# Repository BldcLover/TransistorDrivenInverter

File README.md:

# TransistorDrivenInverter
 Controlling mosfet using transistor logic.

 Here is the testing Video:
 https://youtube.com/shorts/wIxtIQQuSTw

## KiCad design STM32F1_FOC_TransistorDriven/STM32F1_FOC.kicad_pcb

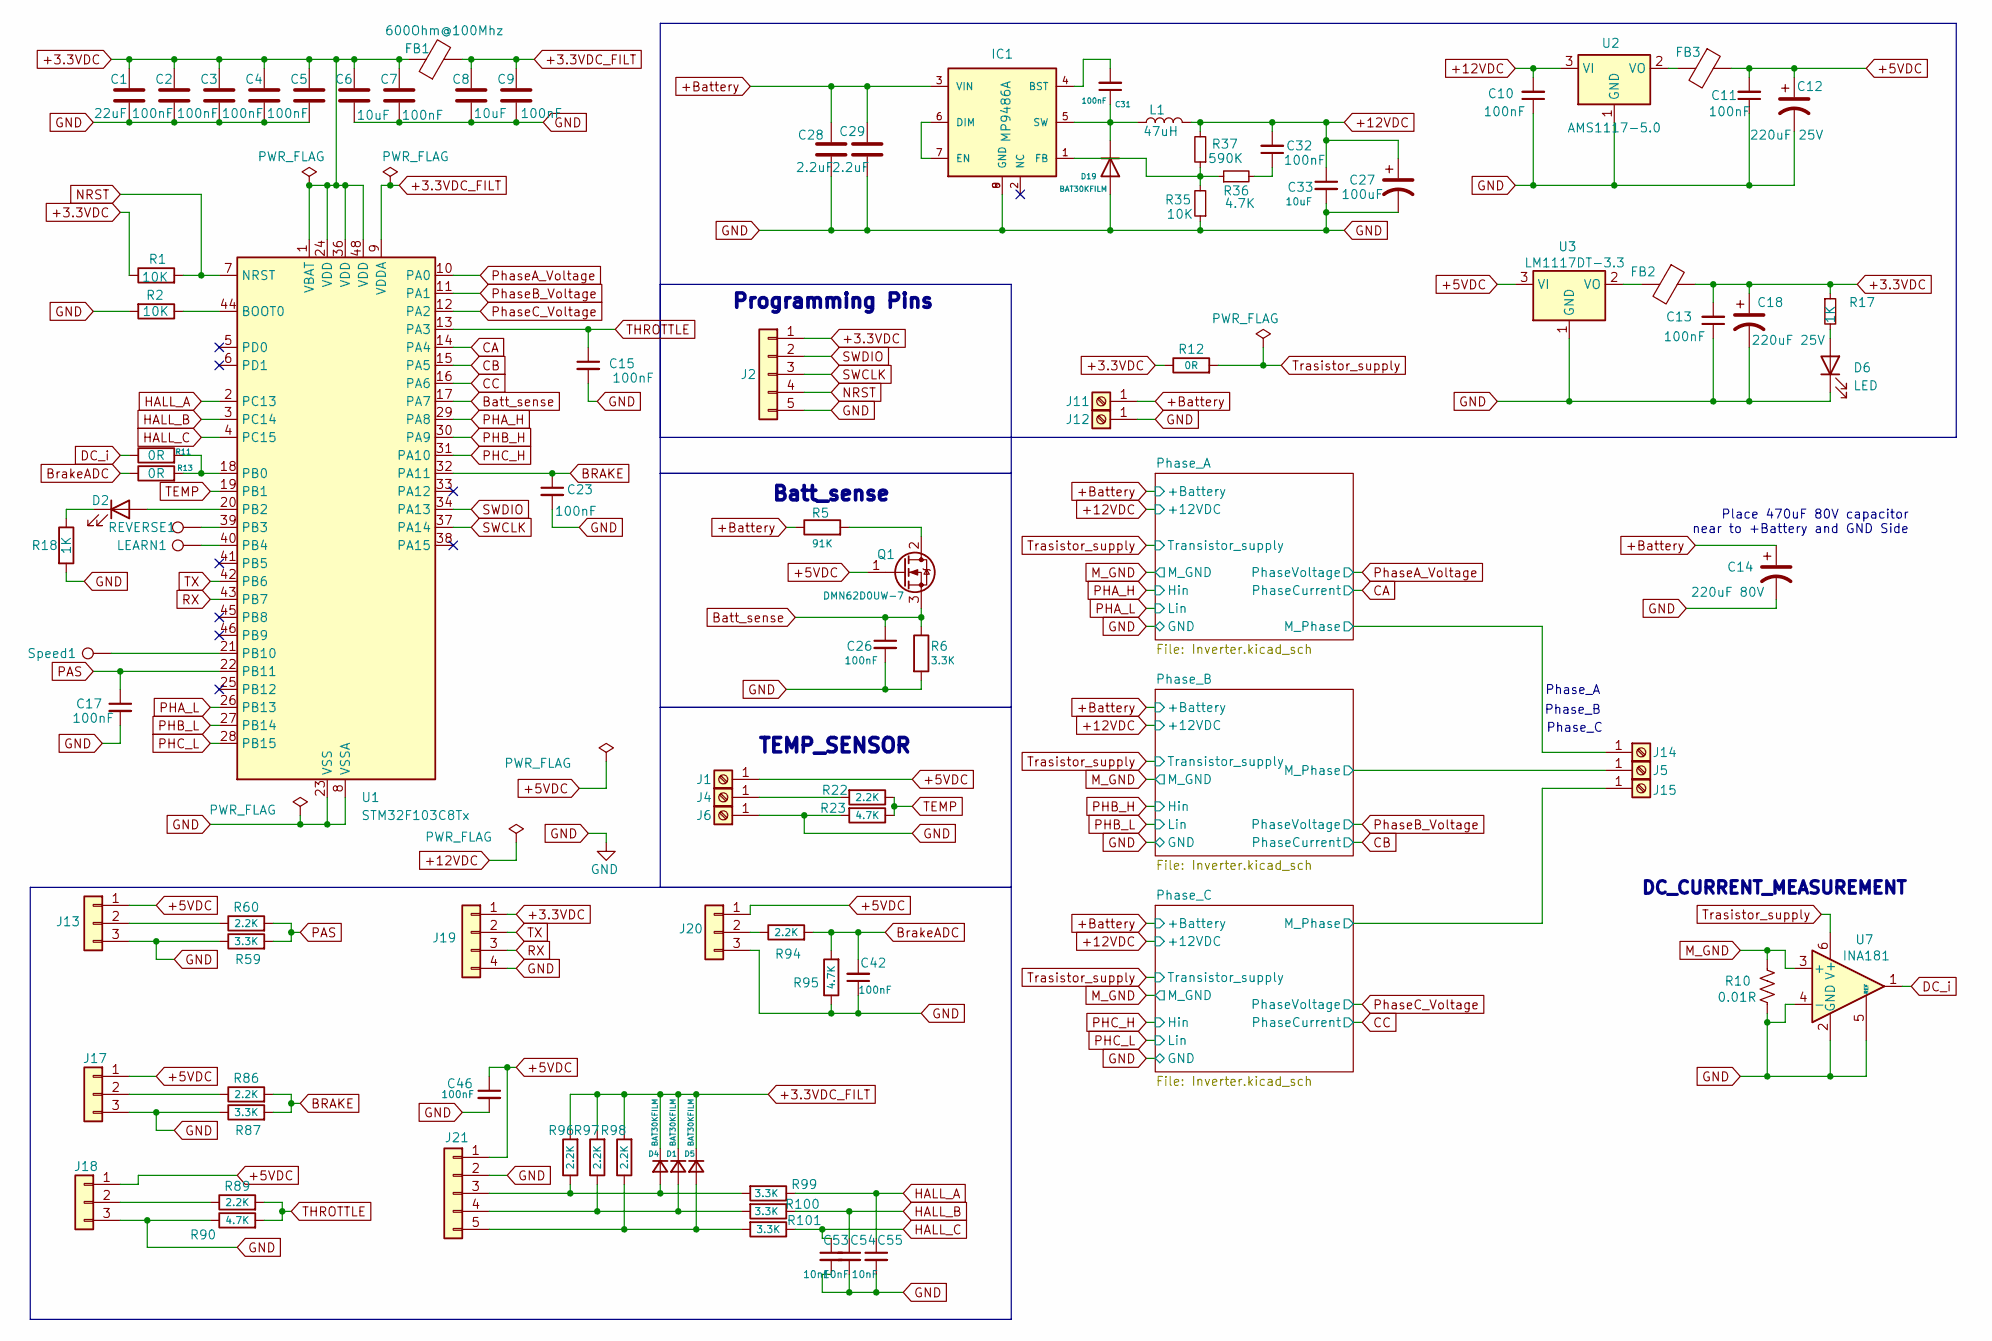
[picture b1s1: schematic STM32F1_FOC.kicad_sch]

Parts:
C1: 22uF; c_0805_CAPC2012X140N
C2, C3, C4, C5, C7, C9, C10, C11, C13, C15, C17, C23, C26, C31, C32, C42, C46: 100nF; C_0603
C6, C8: 10uF; C_0603
C12, C18: 220uF 25V; 220uF25v_DigiKey
C14: 220uF 80V; 220uF_80VDC
C27: 100uF; 100uF25V_UCZ1E101MCL1GS
C28, C29: 2.2uF; 1206_C
C33: 10uF; 1206_C
C53, C54, C55: 10nF; C_0603
D1, D4, D5: BAT30KFILM; D_SOD-523
D2: DebugLed; LED_0603
D6: LED; LED_0603
D19: BAT30KFILM; P38_SOD-523
FB1: 600Ohm@100Mhz; BLM21SP471SN1D
FB2, FB3: BLM21SP471SN1D
IC1: MP9486A; MP9486AGN-Z
J1, J4, J6: Screw_Terminal_01x01; TestPoint_Pad_D1.5mm
J2, J21: Conn_01x05; Socket_Strip_Straight_1x05_Pitch2.54mm
J5, J11, J12, J14, J15: Screw_Terminal_01x01; Hole_4mmx4mm
J13, J17, J18, J20: Conn_01x03; Socket_Strip_Straight_1x03_Pitch2.54mm
J19: Conn_01x04; Socket_Strip_Straight_1x04_Pitch2.54mm
L1: 47uH; 47uH_1Amp_IND_VLS5045EX-470M
LEARN1: TestPoint; TestPoint_Pad_D1.5mm
Q1: DMN62D0UW-7; SOT-323_SC-70_Handsoldering
R1, R2, R35: 10K; R_0603
R5: 91K; R_0603
R6, R59, R87, R99, R100, R101: 3.3K; R_0603
R10: 0.01R; 3_milli_ohm__RESC6330X90N
R11, R13: 0R; R_0603
R12: 0R; SolderJumper-2_P1.3mm_Open_Pad1.0x1.5mm
R17, R18: 1K; R_0603
R22, R60, R86, R89, R94, R96, R97, R98: 2.2K; R_0603
R23, R36, R90, R95: 4.7K; R_0603
R37: 590K; R_0603
REVERSE1: TestPoint; TestPoint_Pad_D1.5mm
Speed1: TestPoint; TestPoint_Pad_D1.5mm
U1: STM32F103C8Tx; LQFP-48_7x7mm_P0.5mm
U2: AMS1117-5.0; SOT-223-3_TabPin2
U3: LM1117DT-3.3; SOT-223-3_TabPin2
U7: INA181; SOT-23-6

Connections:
+3.3VDC: C1.1, C2.1, C3.1, C4.1, C5.1, C6.1, C7.1, C13.2, C18.1, FB1.1, FB2.1, J2.1, J19.1, R1.1, R12.1, R17.1, U1.1 (VBAT), U1.24 (VDD), U1.36 (VDD), U1.48 (VDD)
+3.3VDC_FILT: C8.1, C9.1, D1.1 (K), D4.1 (K), D5.1 (K), FB1.2, R96.2, R97.2, R98.2, U1.9 (VDDA)
+5VDC: C11.2, C12.1, C46.1, FB3.1, J1.1, J13.1, J17.1, J18.1, J20.1, J21.1, Q1.1 (G), U3.3 (VI)
+12VDC: C10.2, C27.1, C32.2, C33.1, L1.2, R37.2, U2.3 (VI); also elsewhere on the board
+Battery: C14.1, C28.1, C29.1, IC1.3 (VIN), J11.1, R5.1; also elsewhere on the board
/Phase_A/M_Phase: J14.1; also elsewhere on the board
/Phase_B/M_Phase: J5.1; also elsewhere on the board
/Phase_C/M_Phase: J15.1; also elsewhere on the board
BRAKE: C23.1, R86.2, R87.2, U1.32 (PA11)
Batt_sense: C26.1, Q1.3 (S), R6.1, U1.17 (PA7)
BrakeADC: C42.2, R13.1, R94.2, R95.2
CA: U1.14 (PA4); also elsewhere on the board
CB: U1.15 (PA5); also elsewhere on the board
CC: U1.16 (PA6); also elsewhere on the board
DC_i: R11.1, U7.1; also elsewhere on the board
GND: C1.2, C2.2, C3.2, C4.2, C5.2, C6.2, C7.2, C8.2, C9.2, C10.1, C11.1, C12.2, C13.1, C14.2, C15.2, C17.2, C18.2, C23.2, C26.2, C27.2, C28.2, C29.2, C33.2, C42.1, C46.2, C53.2, C54.2, C55.2, D6.1 (K), D19.2 (A), IC1.8 (GND), IC1.9 (GND), J2.5, J6.1, J12.1, J13.3, J17.3, J18.3, J19.4, J20.3, J21.2, R2.2, R6.2, R10.2, R18.2, R23.2, R35.1, R59.1, R87.1, R90.1, R95.1, U1.8 (VSSA), U1.23 (VSS), U1.35 (VSS), U1.47 (VSS), U2.1 (GND), U3.1 (GND), U7.2 (GND), U7.4 (-), U7.5 (REF); also elsewhere on the board
HALL_A: C55.1, R99.1, U1.2 (PC13)
HALL_B: C54.1, R100.1, U1.3 (PC14)
HALL_C: C53.1, R101.1, U1.4 (PC15)
M_GND: R10.1, U7.3 (+); also elsewhere on the board
NRST: J2.4, R1.2, U1.7 (NRST)
unnamed: C32.1, R36.2
unnamed: D1.2 (A), J21.4, R97.1, R100.2
unnamed: D2.2 (A), U1.20 (PB2)
unnamed: D2.1 (K), R18.1
unnamed: D4.2 (A), J21.3, R96.1, R99.2
unnamed: D5.2 (A), J21.5, R98.1, R101.2
unnamed: D6.2 (A), R17.2
unnamed: C31.1, D19.1 (K), IC1.5 (SW), L1.1
unnamed: C31.2, IC1.4 (BST)
unnamed: IC1.6 (DIM), IC1.7 (EN)
unnamed: IC1.1 (FB), R35.2, R36.1, R37.1
unnamed: J4.1, R22.2
unnamed: J13.2, R60.1
unnamed: J17.2, R86.1
unnamed: J18.2, R89.1
unnamed: J20.2, R94.1
unnamed: Q1.2 (D), R5.2
unnamed: R2.1, U1.44 (BOOT0)
unnamed: R11.2, R13.2, U1.18 (PB0)
unnamed: REVERSE1.1, U1.39 (PB3)
unnamed: LEARN1.1, U1.40 (PB4)
unnamed: Speed1.1, U1.21 (PB10)
unnamed: FB3.2, U2.2 (VO)
unnamed: FB2.2, U3.2 (VO)
PAS: C17.1, R59.2, R60.2, U1.22 (PB11)
PHA_H: U1.29 (PA8); also elsewhere on the board
PHA_L: U1.26 (PB13); also elsewhere on the board
PHB_H: U1.30 (PA9); also elsewhere on the board
PHB_L: U1.27 (PB14); also elsewhere on the board
PHC_H: U1.31 (PA10); also elsewhere on the board
PHC_L: U1.28 (PB15); also elsewhere on the board
PhaseA_Voltage: U1.10 (PA0); also elsewhere on the board
PhaseB_Voltage: U1.11 (PA1); also elsewhere on the board
PhaseC_Voltage: U1.12 (PA2); also elsewhere on the board
RX: J19.3, U1.43 (PB7)
SWCLK: J2.3, U1.37 (PA14)
SWDIO: J2.2, U1.34 (PA13)
TEMP: R22.1, R23.1, U1.19 (PB1)
THROTTLE: C15.1, R89.2, R90.2, U1.13 (PA3)
TX: J19.2, U1.42 (PB6)
Trasistor_supply: R12.2, U7.6 (V+); also elsewhere on the board

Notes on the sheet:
Phase_C
Phase_A
Programming Pins
DC_CURRENT_MEASUREMENT
Place 470uF 80V capacitor near to +Battery and GND Side
Phase_B
TEMP_SENSOR
Batt_sense

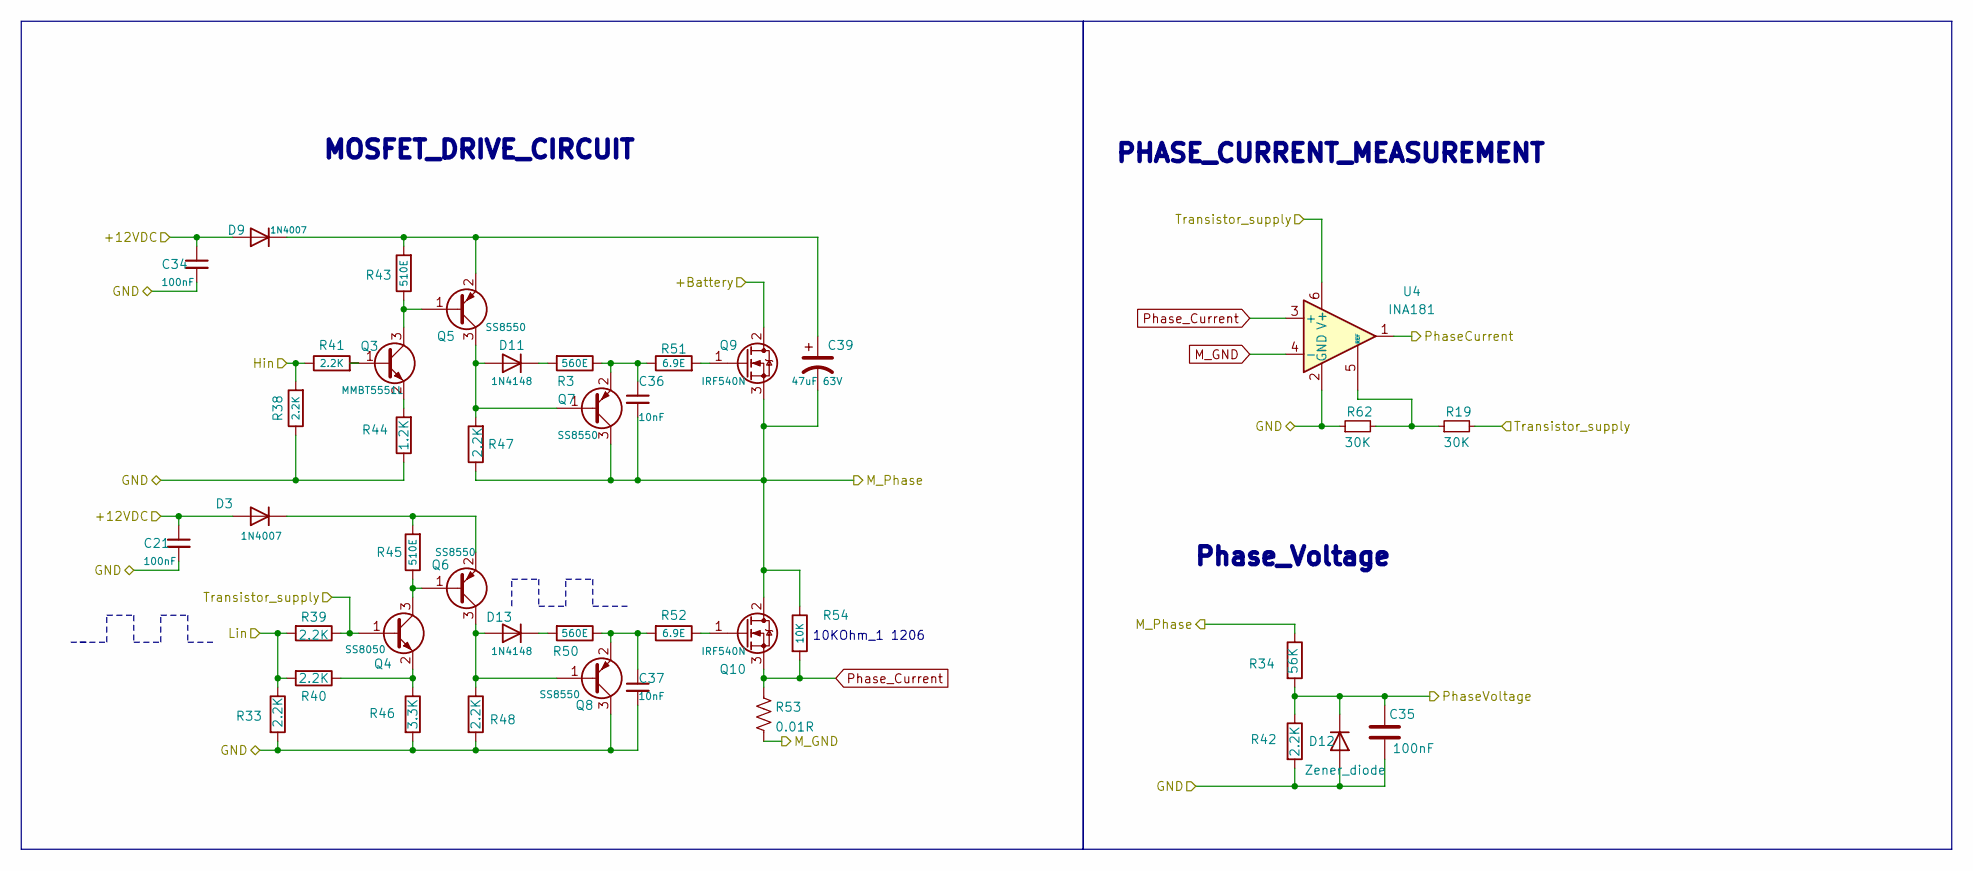
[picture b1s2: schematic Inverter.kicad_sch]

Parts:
C21, C34, C35: 100nF; C_0603
C36, C37: 10nF; C_0603
C39: 47uF 63V; 47uF_25V
D3, D9: 1N4007; M7_D0214AC_DIOM505270X240
D11, D13: 1N4148; P38_SOD-523
D12: Zener_diode; P38_SOD-523
Q3: MMBT5551L; SOT-23_v1
Q4: SS8050; SOT-23_v1
Q5, Q6, Q7, Q8: SS8550; SOT-23_v1
Q9, Q10: IRF540N; TO-220-3_Vertical
R3, R50: 560E; R_0603
R19, R62: 30K; R_0603
R33, R38, R39, R40, R41, R42, R47, R48: 2.2K; R_0603
R34: 56K; R_0603
R43, R45: 510E; R_0603
R44: 1.2K; R_0603
R46: 3.3K; R_0603
R51, R52: 6.9E; R_0603
R53: 0.01R; 3_milli_ohm__RESC6330X90N
R54: 10K; 1206_R
U4: INA181; SOT-23-6

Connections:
+12VDC: C21.1, C34.1, D3.2 (A), D9.2 (A); also elsewhere on the board
+Battery: Q9.2 (D); also elsewhere on the board
/Phase_B/M_Phase: C36.2, C39.2, Q7.3 (C), Q9.3 (S), Q10.2 (D), R34.1, R47.1, R54.1; also elsewhere on the board
CB: U4.1; also elsewhere on the board
GND: C21.2, C34.2, C35.2, C37.2, D12.2 (A), Q8.3 (C), R33.2, R38.1, R42.2, R44.1, R46.2, R48.2, R62.1, U4.2 (GND); also elsewhere on the board
M_GND: R53.2, U4.4 (-); also elsewhere on the board
unnamed: D3.1 (K), Q6.2 (E), R45.2
unnamed: C39.1, D9.1 (K), Q5.2 (E), R43.2
unnamed: D11.2 (A), Q5.3 (C), Q7.1 (B), R47.2
unnamed: D11.1 (K), R3.2
unnamed: D13.2 (A), Q6.3 (C), Q8.1 (B), R48.1
unnamed: D13.1 (K), R50.2
unnamed: Q3.1 (B), R41.2
unnamed: Q3.3 (C), Q5.1 (B), R43.1
unnamed: Q3.2 (E), R44.2
unnamed: Q4.3 (C), Q6.1 (B), R45.1
unnamed: Q4.2 (E), R40.1, R46.1
unnamed: C36.1, Q7.2 (E), R3.1, R51.1
unnamed: C37.1, Q8.2 (E), R50.1, R52.2
unnamed: Q9.1 (G), R51.2
unnamed: Q10.1 (G), R52.1
unnamed: R19.1, R62.2, U4.5 (REF)
PHB_H: R38.2, R41.1; also elsewhere on the board
PHB_L: R33.1, R39.2, R40.2; also elsewhere on the board
PhaseB_Voltage: C35.1, D12.1 (K), R34.2, R42.1; also elsewhere on the board
Phase_Current: Q10.3 (S), R53.1, R54.2, U4.3 (+); also elsewhere on the board
Trasistor_supply: Q4.1 (B), R19.2, R39.1, U4.6 (V+); also elsewhere on the board

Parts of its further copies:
C22, C45, C47, C48, C90, C95: 100nF; C_0603
C49, C50, C92, C93: 10nF; C_0603
C52, C94: 47uF 63V; 47uF_25V
D7, D10, D22, D23: 1N4007; M7_D0214AC_DIOM505270X240
D16, D17, D32, D33: 1N4148; P38_SOD-523
D20, D21: Zener_diode; P38_SOD-523
Q12, Q32: MMBT5551L; SOT-23_v1
Q13, Q33: SS8050; SOT-23_v1
Q15, Q16, Q17, Q18, Q34, Q35, Q36, Q37: SS8550; SOT-23_v1
Q19, Q20, Q38, Q39: IRF540N; TO-220-3_Vertical
R4, R7, R80, R150: 560E; R_0603
R56, R57, R63, R65: 30K; R_0603
R66, R68, R69, R70, R71, R72, R77, R78, R137, R138, R139, R140, R141, R147, R148, R157: 2.2K; R_0603
R67, R156: 56K; R_0603
R73, R75, R142, R144: 510E; R_0603
R74, R143: 1.2K; R_0603
R76, R145: 3.3K; R_0603
R81, R82, R152, R153: 6.9E; R_0603
R83, R129: 0.01R; 3_milli_ohm__RESC6330X90N
R84, R155: 10K; 1206_R
U5, U6: INA181; SOT-23-6

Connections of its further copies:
+12VDC: C22.1, C45.1, C47.1, C90.1, D7.2 (A), D10.2 (A), D22.2 (A), D23.2 (A); also elsewhere on the board
+Battery: Q19.2 (D), Q38.2 (D); also elsewhere on the board
/Phase_A/M_Phase: C92.2, C94.2, Q36.3 (C), Q38.3 (S), Q39.2 (D), R147.1, R155.1, R156.1; also elsewhere on the board
/Phase_C/M_Phase: C49.2, C52.2, Q17.3 (C), Q19.3 (S), Q20.2 (D), R67.1, R77.1, R84.1; also elsewhere on the board
CA: U6.1; also elsewhere on the board
CC: U5.1; also elsewhere on the board
GND: C22.2, C45.2, C47.2, C48.2, C50.2, C90.2, C93.2, C95.2, D20.2 (A), D21.2 (A), Q18.3 (C), Q37.3 (C), R63.1, R65.1, R66.2, R68.1, R72.2, R74.1, R76.2, R78.2, R137.2, R140.1, R143.1, R145.2, R148.2, R157.2, U5.2 (GND), U6.2 (GND); also elsewhere on the board
M_GND: R83.2, R129.2, U5.4 (-), U6.4 (-); also elsewhere on the board
unnamed: D7.1 (K), Q16.2 (E), R75.2
unnamed: D10.1 (K), Q35.2 (E), R144.2
unnamed: D16.2 (A), Q15.3 (C), Q17.1 (B), R77.2
unnamed: D16.1 (K), R4.2
unnamed: D17.2 (A), Q16.3 (C), Q18.1 (B), R78.1
unnamed: D17.1 (K), R80.2
unnamed: C52.1, D22.1 (K), Q15.2 (E), R73.2
unnamed: C94.1, D23.1 (K), Q34.2 (E), R142.2
unnamed: D32.2 (A), Q34.3 (C), Q36.1 (B), R147.2
unnamed: D32.1 (K), R7.2
unnamed: D33.2 (A), Q35.3 (C), Q37.1 (B), R148.1
unnamed: D33.1 (K), R150.2
unnamed: Q12.1 (B), R71.2
unnamed: Q12.3 (C), Q15.1 (B), R73.1
unnamed: Q12.2 (E), R74.2
unnamed: Q13.3 (C), Q16.1 (B), R75.1
unnamed: Q13.2 (E), R70.1, R76.1
unnamed: C49.1, Q17.2 (E), R4.1, R81.1
unnamed: C50.1, Q18.2 (E), R80.1, R82.2
unnamed: Q19.1 (G), R81.2
unnamed: Q20.1 (G), R82.1
unnamed: Q32.1 (B), R141.2
unnamed: Q32.3 (C), Q34.1 (B), R142.1
unnamed: Q32.2 (E), R143.2
unnamed: Q33.3 (C), Q35.1 (B), R144.1
unnamed: Q33.2 (E), R139.1, R145.1
unnamed: C92.1, Q36.2 (E), R7.1, R153.1
unnamed: C93.1, Q37.2 (E), R150.1, R152.2
unnamed: Q38.1 (G), R153.2
unnamed: Q39.1 (G), R152.1
unnamed: R56.1, R63.2, U5.5 (REF)
unnamed: R57.1, R65.2, U6.5 (REF)
PHA_H: R140.2, R141.1; also elsewhere on the board
PHA_L: R137.1, R138.2, R139.2; also elsewhere on the board
PHC_H: R68.2, R71.1; also elsewhere on the board
PHC_L: R66.1, R69.2, R70.2; also elsewhere on the board
PhaseA_Voltage: C95.1, D21.1 (K), R156.2, R157.1; also elsewhere on the board
PhaseC_Voltage: C48.1, D20.1 (K), R67.2, R72.1; also elsewhere on the board
Phase_Current: Q20.3 (S), Q39.3 (S), R83.1, R84.2, R129.1, R155.2, U5.3 (+), U6.3 (+); also elsewhere on the board
Trasistor_supply: Q13.1 (B), Q33.1 (B), R56.2, R57.2, R69.1, R138.1, U5.6 (V+), U6.6 (V+); also elsewhere on the board

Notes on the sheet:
MOSFET_DRIVE_CIRCUIT
Phase_Voltage
PHASE_CURRENT_MEASUREMENT
10KOhm_1 1206

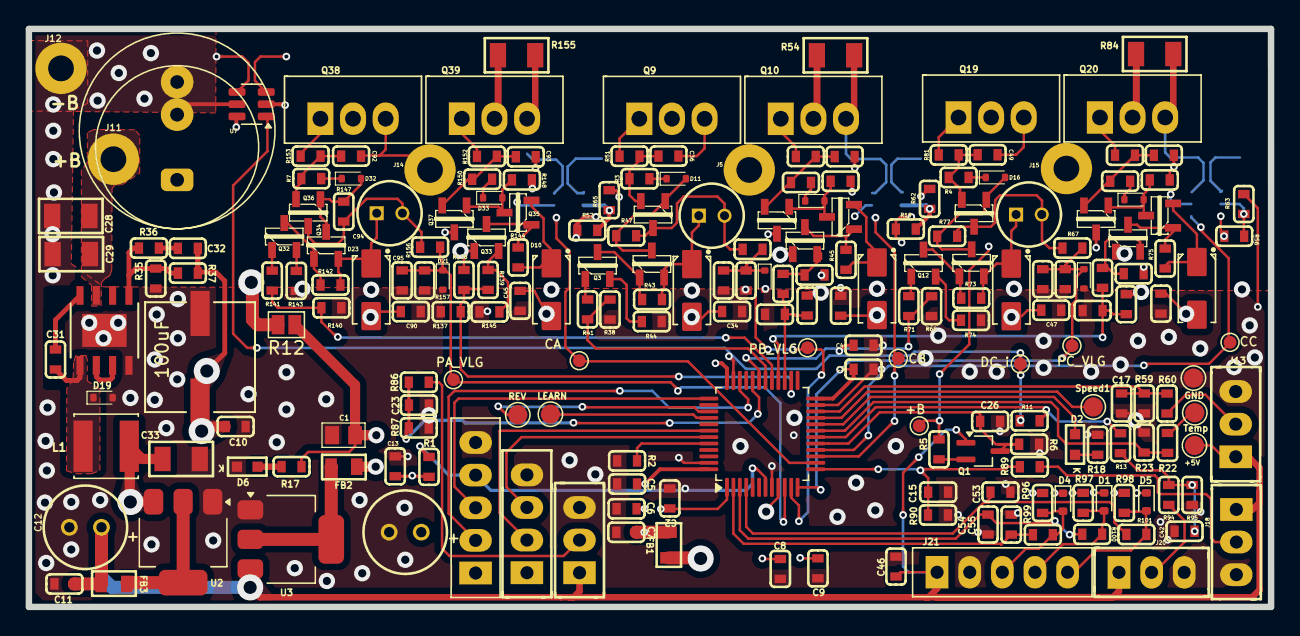
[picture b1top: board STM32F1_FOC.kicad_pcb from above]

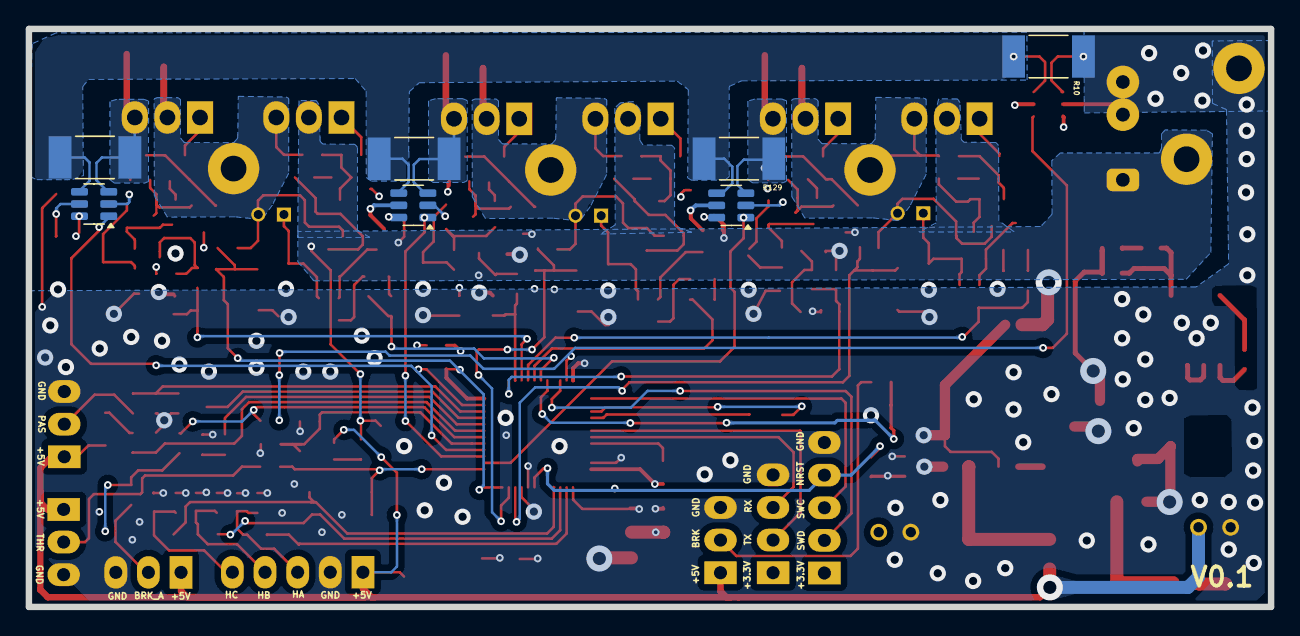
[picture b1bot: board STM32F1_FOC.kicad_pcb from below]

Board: 4 copper layers, 96.7 x 45.0 mm, 224 parts (7 on the bottom side), 111 nets.

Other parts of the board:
PA_VLG: TestPoint_Pad_D1.0mm
PA_VLG#2, PA_VLG#3, PA_VLG#4, PA_VLG#5, PA_VLG#6: TestPoint_Pad_D1.0mm
PB_VLG: TestPoint_Pad_D1.0mm
PC_VLG: TestPoint_Pad_D1.0mm

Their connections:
+Battery: PA_VLG#2.1; also elsewhere on the board
CA: PA_VLG#6.1; also elsewhere on the board
CB: PA_VLG#3.1; also elsewhere on the board
CC: PA_VLG#4.1; also elsewhere on the board
DC_i: PA_VLG#5.1; also elsewhere on the board
PhaseA_Voltage: PA_VLG.1; also elsewhere on the board
PhaseB_Voltage: PB_VLG.1; also elsewhere on the board
PhaseC_Voltage: PC_VLG.1; also elsewhere on the board

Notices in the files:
parts and their libraries:
Copyright 2016 Accelerated Designs. All rights reserved.
